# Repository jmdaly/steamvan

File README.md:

# SteamVan PCB

The SteamVan was developed as a MiniVan-compatible PCB based on an STM32MCU. It
does not support hot swap sockets, and it is designed such that the switches
are oriented such that the LEDs are South-facing.

## Overview

The SteamVan aims to meet the following design goals:

* Switches oriented such that the LEDs are South-facing, for
  compatibility with Cherry profile keycaps.

* USB Type-C support in both A to C and C to C configurations.

* QMK support.

* ESD protection circuitry, including data line protection and a
  polyfuse on the VCC line.

* Support for per-switch LED backlighting.

* Fits in MiniVan keyboard cases (tested with R3 MiniVan case only)

* RGB LED underglow support.

## Supported Layouts

The SteamVan supports the same layout options as the MiniVan.

## Obtaining the Files

This repository contains several submodules, which in turn contain
KiCad libraries used in the PCB design. In order to clone the SteamVan
repository, and all of the library submodules, the following command
must be issued,

```
git clone --recursive https://github.com/jmdaly/steamvan.git
```

## Acknowledgements

This project would not have been possible without all of the awesome work put
in by Evan Sailer of thevankeyboards.com. I own an R3 MiniVan and I love it. I
really like PCBs that have South-facing LEDs, USB-C connectors, and STM32
microcontrollers. As a result, I took on this project so that I could continue
to use the MiniVan layout, as well as my MiniVan case and keycaps, but have
some of the features that are important to me in a keyboard. I hope this work
is useful to other people.

There is an active keyboard design community on the MechKeys discord. The
users there have been very helpful, and I've learned a significant
amount about PCB design from them.

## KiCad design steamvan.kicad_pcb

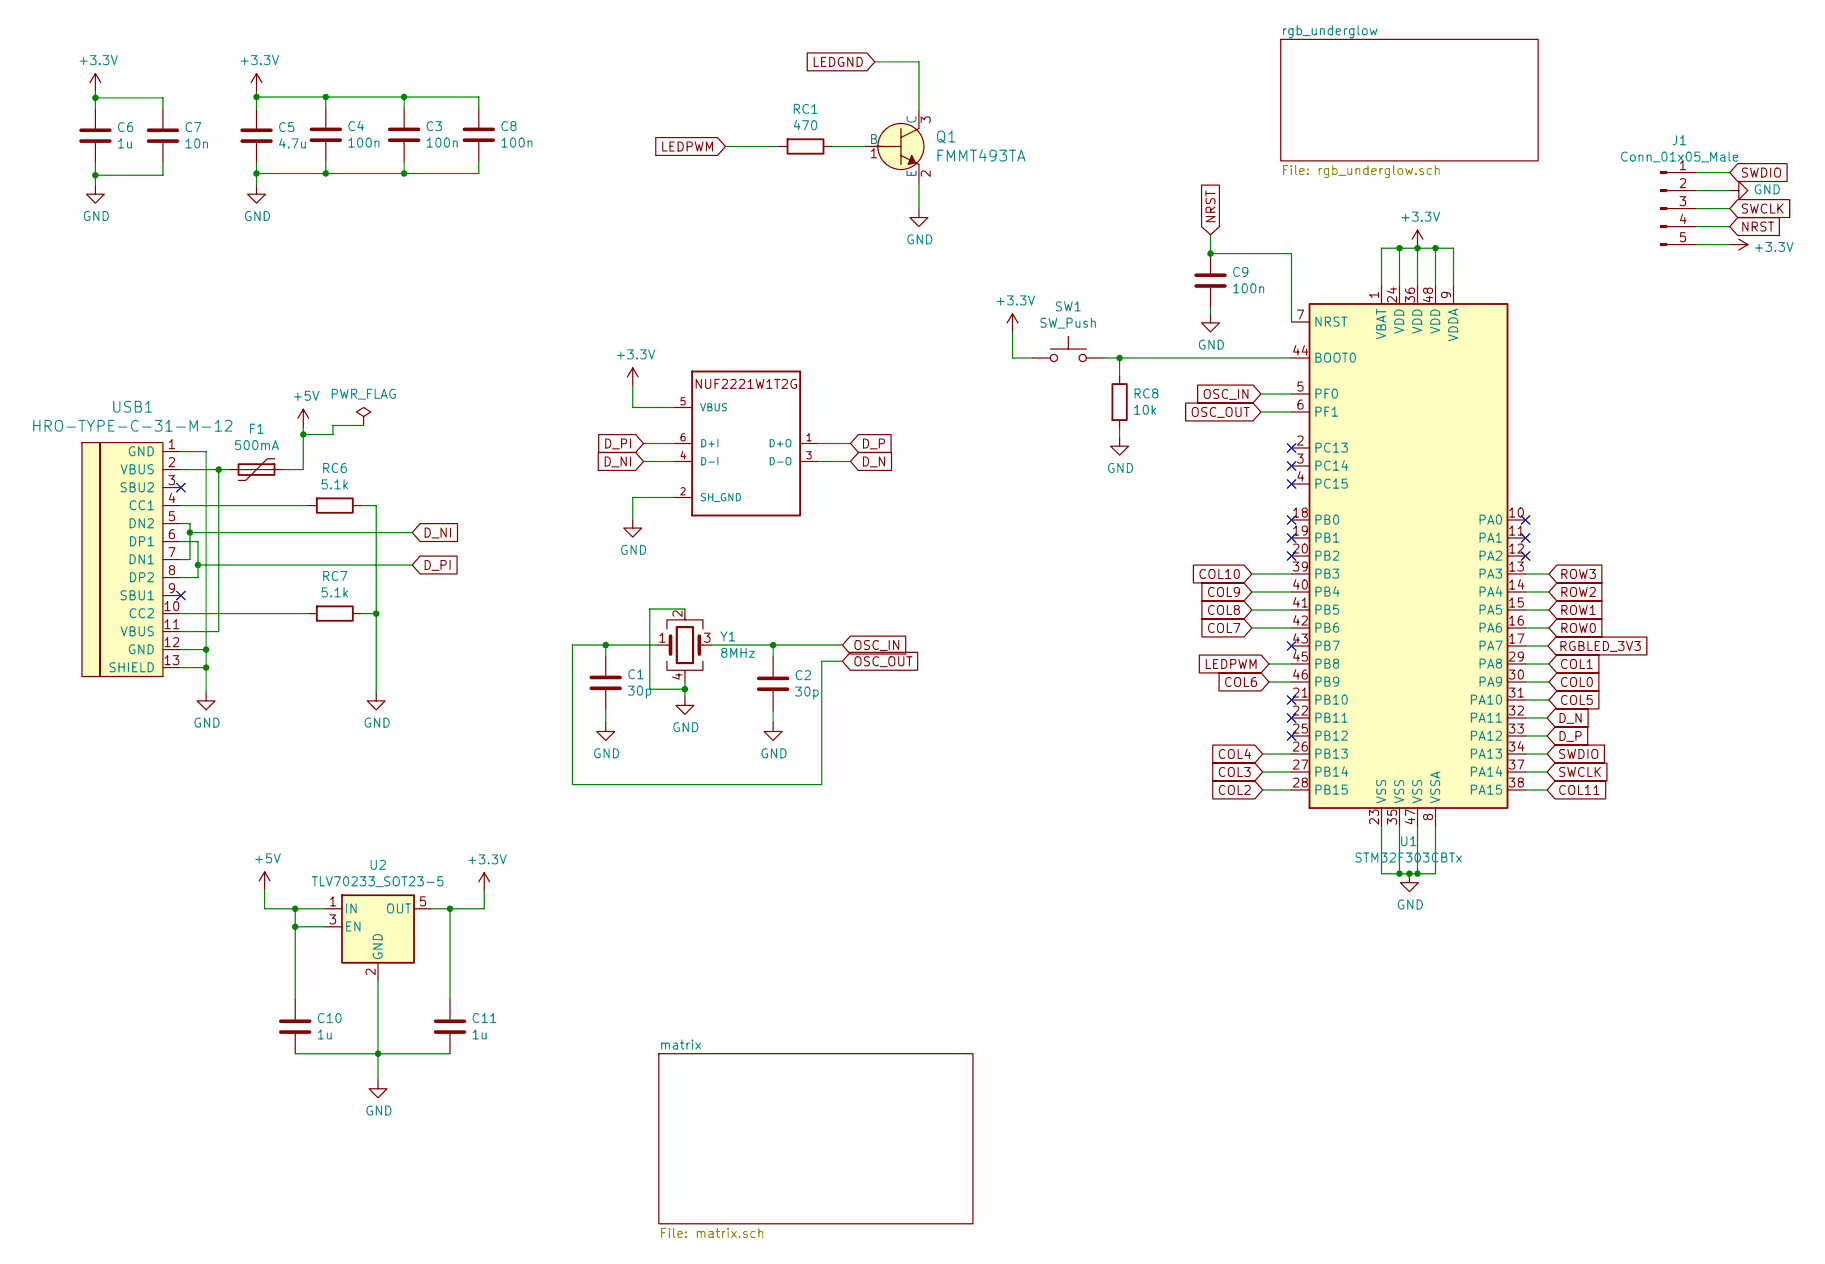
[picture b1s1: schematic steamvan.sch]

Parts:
C1, C2: 30p; C_0603_1608Metric; LCSC PN C22397
C3, C4, C8, C9: 100n; C_0603_1608Metric; LCSC PN C1590
C5: 4.7u; C_0603_1608Metric; LCSC PN C19666
C6, C10, C11: 1u; C_0603_1608Metric; LCSC PN C59782
C7: 10n; C_0603_1608Metric; LCSC PN C1589
F1: 500mA; R_0805_2012Metric; LCSC PN C66452
J1: Conn_01x05_Male; PinHeader_1x05_P2.54mm_Vertical
Q1: FMMT493TA; SOT-23-3; MPN FMMT493TA; Digi-Key_PN FMMT493CT-ND
RC1: 470; R_0603_1608Metric
RC6, RC7: 5.1k; R_0603_1608Metric; LCSC PN C14677
RC8: 10k; R_0603_1608Metric; LCSC PN C98220
SW1: SW_Push; SW_SPST_TL3342; LCSC PN C92584
U1: STM32F303CBTx; LQFP-48_7x7mm_P0.5mm; LCSC PN C108516
U2: TLV70233_SOT23-5; SOT-23-5; LCSC PN C26833
U3: NUF2221W1T2G; SOT-363; LCSC PN C274624
USB1: HRO-TYPE-C-31-M-12; HRO-TYPE-C-31-M-12-Assembly; LCSC PN C165948
Y1: 8MHz; Crystal_SMD_5032-4Pin_5.0x3.2mm; LCSC PN C133333

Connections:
+3V3: C3.1, C4.1, C5.1, C6.1, C7.1, C8.1, C11.1, J1.5, SW1.1, U1.1 (VBAT), U1.9 (VDDA), U1.24 (VDD), U1.36 (VDD), U1.48 (VDD), U2.5 (OUT), U3.5 (VBUS)
+5V: C10.1, F1.1, U2.1 (IN), U2.3 (EN); also elsewhere on the board
COL0: U1.30 (PA9); also elsewhere on the board
COL1: U1.29 (PA8); also elsewhere on the board
COL2: U1.28 (PB15); also elsewhere on the board
COL3: U1.27 (PB14); also elsewhere on the board
COL4: U1.26 (PB13); also elsewhere on the board
COL5: U1.31 (PA10); also elsewhere on the board
COL6: U1.46 (PB9); also elsewhere on the board
COL7: U1.42 (PB6); also elsewhere on the board
COL8: U1.41 (PB5); also elsewhere on the board
COL9: U1.40 (PB4); also elsewhere on the board
COL10: U1.39 (PB3); also elsewhere on the board
COL11: U1.38 (PA15); also elsewhere on the board
D_N: U1.32 (PA11), U3.3 (D-O)
D_NI: U3.4 (D-I), USB1.5 (DN2), USB1.7 (DN1)
D_P: U1.33 (PA12), U3.1 (D+O)
D_PI: U3.6 (D+I), USB1.6 (DP1), USB1.8 (DP2)
GND: C1.2, C2.2, C3.2, C4.2, C5.2, C6.2, C7.2, C8.2, C9.2, C10.2, C11.2, J1.2, Q1.2 (E), RC6.1, RC7.1, RC8.2, U1.8 (VSSA), U1.23 (VSS), U1.35 (VSS), U1.47 (VSS), U2.2 (GND), U3.2 (SH_GND), USB1.1 (GND), USB1.12 (GND), USB1.13 (SHIELD), Y1.2, Y1.4; also elsewhere on the board
LEDGND: Q1.3 (C); also elsewhere on the board
LEDPWM: RC1.2, U1.45 (PB8)
NRST: C9.1, J1.4, U1.7 (NRST)
unnamed: F1.2, USB1.2 (VBUS), USB1.11 (VBUS)
unnamed: Q1.1 (B), RC1.1
unnamed: RC6.2, USB1.4 (CC1)
unnamed: RC7.2, USB1.10 (CC2)
unnamed: RC8.1, SW1.2, U1.44 (BOOT0)
OSC_IN: C2.1, U1.5 (PF0), Y1.3
OSC_OUT: C1.1, U1.6 (PF1), Y1.1
RGBLED_3V3: U1.17 (PA7); also elsewhere on the board
ROW0: U1.16 (PA6); also elsewhere on the board
ROW1: U1.15 (PA5); also elsewhere on the board
ROW2: U1.14 (PA4); also elsewhere on the board
ROW3: U1.13 (PA3); also elsewhere on the board
SWCLK: J1.3, U1.37 (PA14)
SWDIO: J1.1, U1.34 (PA13)

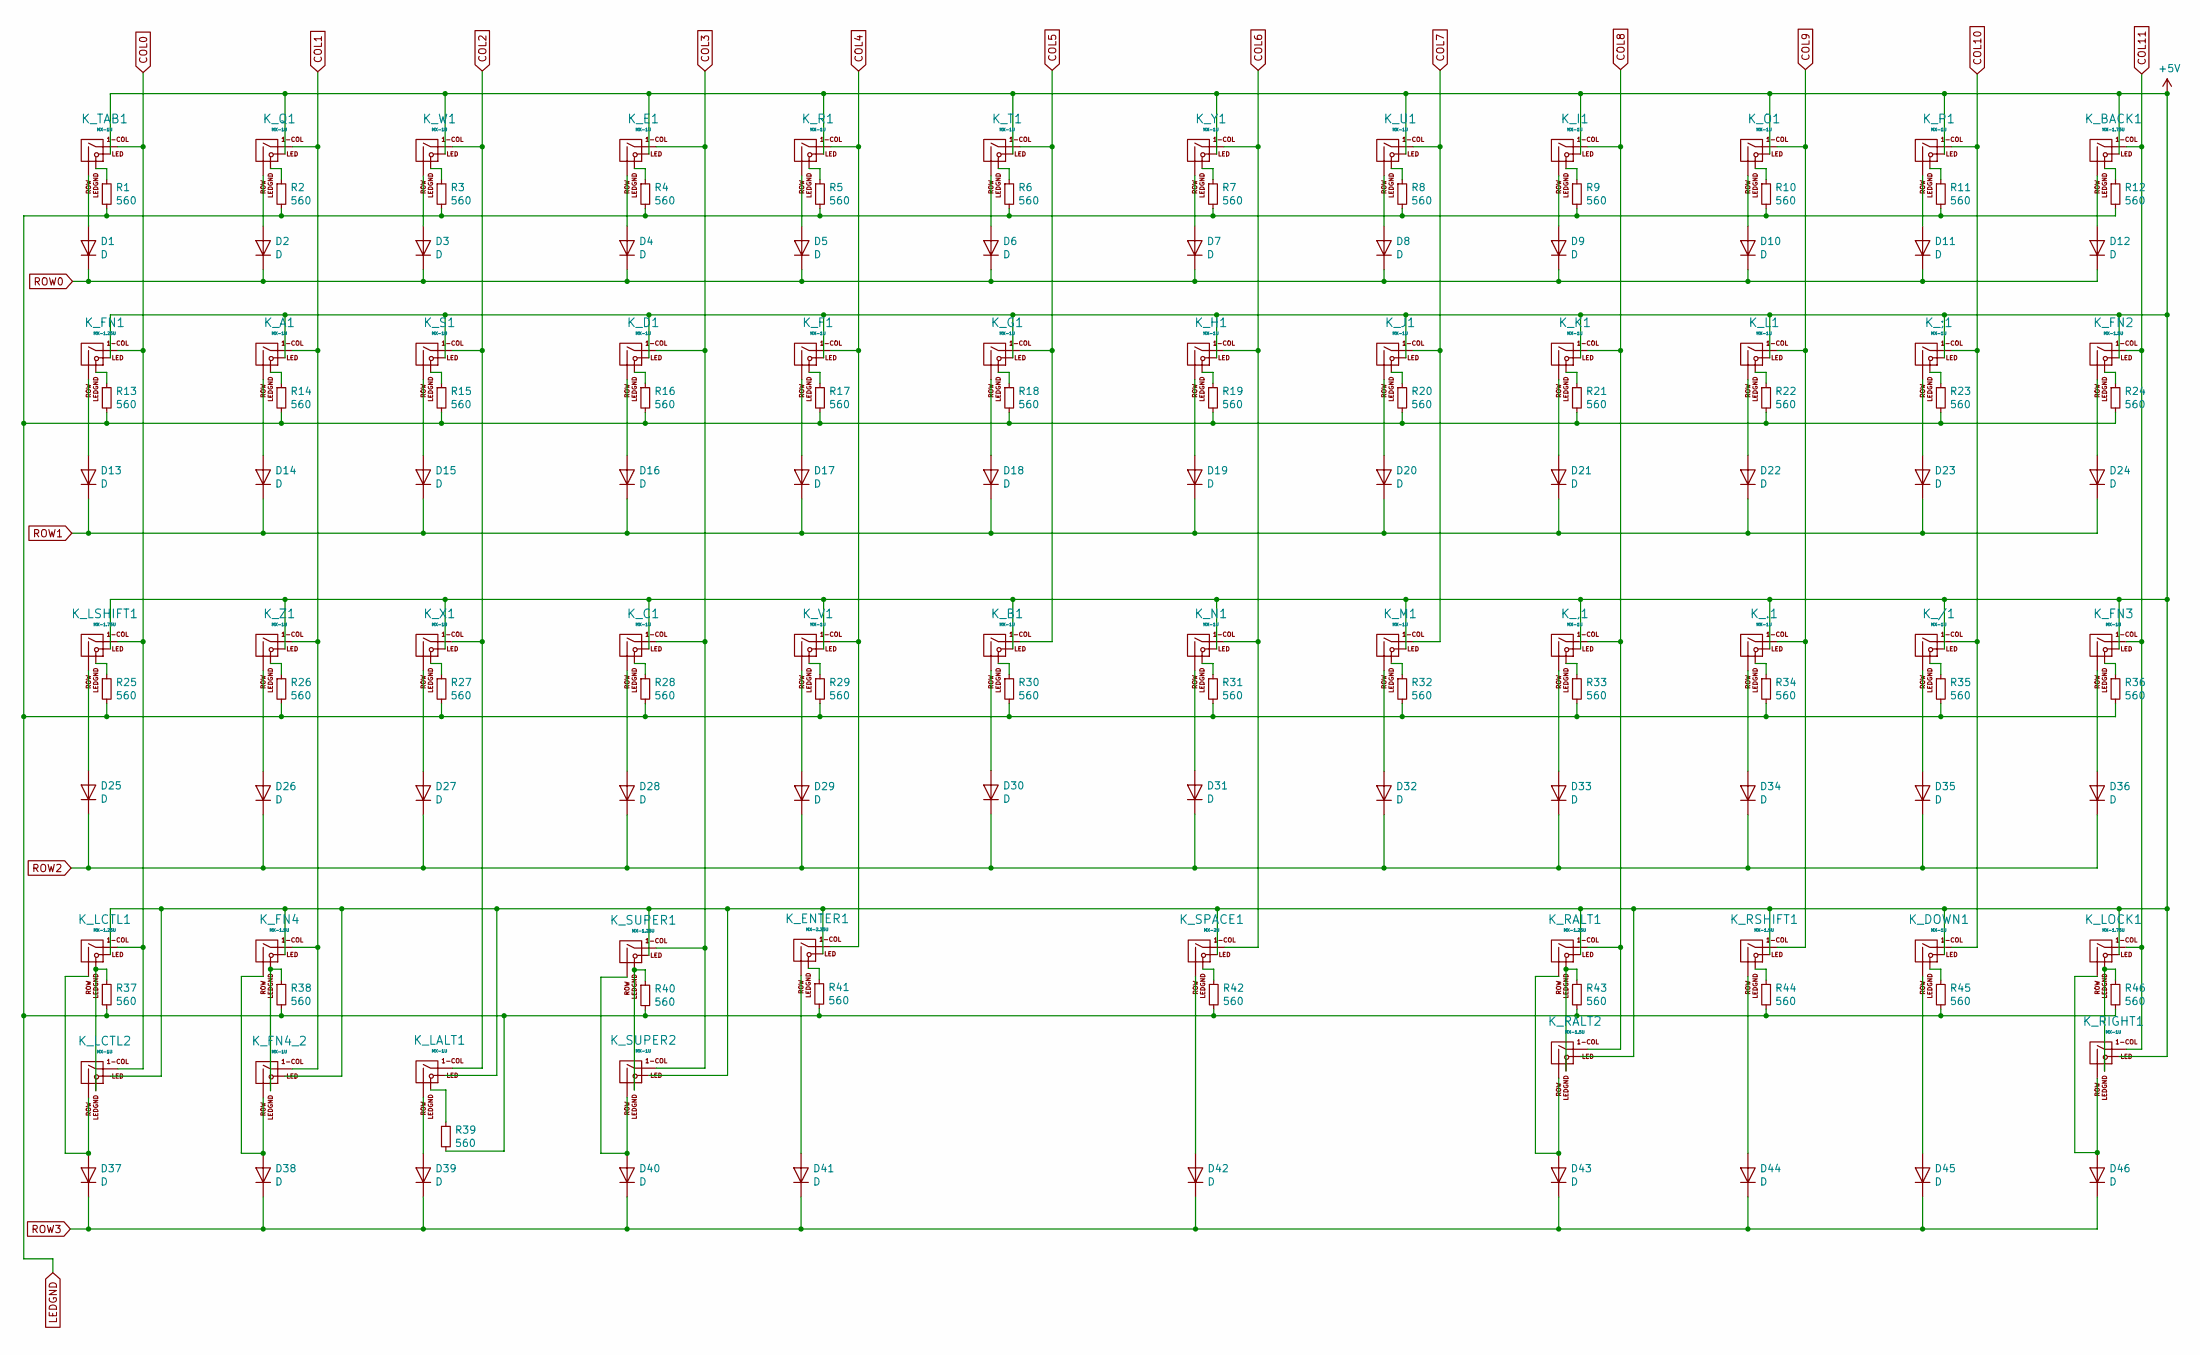
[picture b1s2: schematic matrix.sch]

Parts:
D1, D2, D3, D4, D5, D6, D7, D8, D9, D10, D11, D12, D13, D14, D15, D16, D17, D18, D19, D20, D21, D22, D23, D24, D25, D26, D27, D28, D29, D30, D31, D32, D33, D34, D35, D36, D37, D38, D39, D40, D41, D42, D43, D44, D45, D46: D; D_SOD-123; LCSC PN C83528
K_,1: MX-1U; MXOnly-1U
K_.1: MX-1U; MXOnly-1U
K_/1: MX-1U; MXOnly-1U
K_;1: MX-1U; MXOnly-1U
K_A1: MX-1U; MXOnly-1U
K_B1: MX-1U; MXOnly-1U
K_BACK1: MX-1.75U; MXOnly-1.75U
K_C1: MX-1U; MXOnly-1U
K_D1: MX-1U; MXOnly-1U
K_DOWN1: MX-1U; MXOnly-1U
K_E1: MX-1U; MXOnly-1U
K_ENTER1: MX-2.25U; MXOnly-2.25U-ReversedStabilizers
K_F1: MX-1U; MXOnly-1U
K_FN1: MX-1.25U; MXOnly-1.25U
K_FN2, K_FN4: MX-1.5U; MXOnly-1.5U
K_FN3, K_FN4_2: MX-1U; MXOnly-1U
K_G1: MX-1U; MXOnly-1U
K_H1: MX-1U; MXOnly-1U
K_I1: MX-1U; MXOnly-1U
K_J1: MX-1U; MXOnly-1U
K_K1: MX-1U; MXOnly-1U
K_L1: MX-1U; MXOnly-1U
K_LALT1: MX-1U; MXOnly-1U
K_LCTL1: MX-1.25U; MXOnly-1.25U
K_LCTL2: MX-1U; MXOnly-1U-FLIPPED
K_LOCK1: MX-1.75U; MXOnly-1.75U
K_LSHIFT1: MX-1.75U; MXOnly-1.75U
K_M1: MX-1U; MXOnly-1U
K_N1: MX-1U; MXOnly-1U
K_O1: MX-1U; MXOnly-1U
K_P1: MX-1U; MXOnly-1U
K_Q1: MX-1U; MXOnly-1U
K_R1: MX-1U; MXOnly-1U
K_RALT1: MX-1.25U; MXOnly-1.25U
K_RALT2: MX-1.5U; MXOnly-1.5U-FLIPPED
K_RIGHT1: MX-1U; MXOnly-1U
K_RSHIFT1: MX-1.5U; MXOnly-1.5U
K_S1: MX-1U; MXOnly-1U
K_SPACE1: MX-2U; MXOnly-2U-ReversedStabilizers
K_SUPER1: MX-1.25U; MXOnly-1.25U
K_SUPER2: MX-1U; MXOnly-1U-FLIPPED
K_T1: MX-1U; MXOnly-1U
K_TAB1: MX-1U; MXOnly-1U
K_U1: MX-1U; MXOnly-1U
K_V1: MX-1U; MXOnly-1U
K_W1: MX-1U; MXOnly-1U
K_X1: MX-1U; MXOnly-1U
K_Y1: MX-1U; MXOnly-1U
K_Z1: MX-1U; MXOnly-1U
R1, R2, R3, R4, R5, R6, R7, R8, R9, R10, R11, R12, R13, R14, R15, R16, R17, R18, R19, R20, R21, R22, R23, R24, R25, R26, R27, R28, R29, R30, R31, R32, R33, R34, R35, R36, R37, R38, R39, R40, R41, R42, R43, R44, R45, R46: 560; R_0603_1608Metric

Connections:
+5V: K_,1.3 (LED), K_.1.3 (LED), K_/1.3 (LED), K_;1.3 (LED), K_A1.3 (LED), K_B1.3 (LED), K_BACK1.3 (LED), K_C1.3 (LED), K_D1.3 (LED), K_DOWN1.3 (LED), K_E1.3 (LED), K_ENTER1.3 (LED), K_F1.3 (LED), K_FN1.3 (LED), K_FN2.3 (LED), K_FN3.3 (LED), K_FN4.3 (LED), K_FN4_2.3 (LED), K_G1.3 (LED), K_H1.3 (LED), K_I1.3 (LED), K_J1.3 (LED), K_K1.3 (LED), K_L1.3 (LED), K_LALT1.3 (LED), K_LCTL1.3 (LED), K_LCTL2.3 (LED), K_LOCK1.3 (LED), K_LSHIFT1.3 (LED), K_M1.3 (LED), K_N1.3 (LED), K_O1.3 (LED), K_P1.3 (LED), K_Q1.3 (LED), K_R1.3 (LED), K_RALT1.3 (LED), K_RALT2.3 (LED), K_RIGHT1.3 (LED), K_RSHIFT1.3 (LED), K_S1.3 (LED), K_SPACE1.3 (LED), K_SUPER1.3 (LED), K_SUPER2.3 (LED), K_T1.3 (LED), K_TAB1.3 (LED), K_U1.3 (LED), K_V1.3 (LED), K_W1.3 (LED), K_X1.3 (LED), K_Y1.3 (LED), K_Z1.3 (LED); also elsewhere on the board
COL0: K_FN1.1 (COL), K_LCTL1.1 (COL), K_LCTL2.1 (COL), K_LSHIFT1.1 (COL), K_TAB1.1 (COL); also elsewhere on the board
COL1: K_A1.1 (COL), K_FN4.1 (COL), K_FN4_2.1 (COL), K_Q1.1 (COL), K_Z1.1 (COL); also elsewhere on the board
COL2: K_LALT1.1 (COL), K_S1.1 (COL), K_W1.1 (COL), K_X1.1 (COL); also elsewhere on the board
COL3: K_C1.1 (COL), K_D1.1 (COL), K_E1.1 (COL), K_SUPER1.1 (COL), K_SUPER2.1 (COL); also elsewhere on the board
COL4: K_ENTER1.1 (COL), K_F1.1 (COL), K_R1.1 (COL), K_V1.1 (COL); also elsewhere on the board
COL5: K_B1.1 (COL), K_G1.1 (COL), K_T1.1 (COL); also elsewhere on the board
COL6: K_H1.1 (COL), K_N1.1 (COL), K_SPACE1.1 (COL), K_Y1.1 (COL); also elsewhere on the board
COL7: K_J1.1 (COL), K_M1.1 (COL), K_U1.1 (COL); also elsewhere on the board
COL8: K_,1.1 (COL), K_I1.1 (COL), K_K1.1 (COL), K_RALT1.1 (COL), K_RALT2.1 (COL); also elsewhere on the board
COL9: K_.1.1 (COL), K_L1.1 (COL), K_O1.1 (COL), K_RSHIFT1.1 (COL); also elsewhere on the board
COL10: K_/1.1 (COL), K_;1.1 (COL), K_DOWN1.1 (COL), K_P1.1 (COL); also elsewhere on the board
COL11: K_BACK1.1 (COL), K_FN2.1 (COL), K_FN3.1 (COL), K_LOCK1.1 (COL), K_RIGHT1.1 (COL); also elsewhere on the board
LEDGND: R1.2, R2.2, R3.2, R4.2, R5.2, R6.2, R7.2, R8.2, R9.2, R10.2, R11.2, R12.2, R13.2, R14.2, R15.2, R16.2, R17.2, R18.2, R19.2, R20.2, R21.2, R22.2, R23.2, R24.2, R25.2, R26.2, R27.2, R28.2, R29.2, R30.2, R31.2, R32.2, R33.2, R34.2, R35.2, R36.2, R37.2, R38.2, R39.2, R40.2, R41.2, R42.2, R43.2, R44.2, R45.2, R46.2; also elsewhere on the board
unnamed: D1.2 (A), K_TAB1.2 (ROW)
unnamed: D2.2 (A), K_Q1.2 (ROW)
unnamed: D3.2 (A), K_W1.2 (ROW)
unnamed: D4.2 (A), K_E1.2 (ROW)
unnamed: D5.2 (A), K_R1.2 (ROW)
unnamed: D6.2 (A), K_T1.2 (ROW)
unnamed: D7.2 (A), K_Y1.2 (ROW)
unnamed: D8.2 (A), K_U1.2 (ROW)
unnamed: D9.2 (A), K_I1.2 (ROW)
unnamed: D10.2 (A), K_O1.2 (ROW)
unnamed: D11.2 (A), K_P1.2 (ROW)
unnamed: D12.2 (A), K_BACK1.2 (ROW)
unnamed: D13.2 (A), K_FN1.2 (ROW)
unnamed: D14.2 (A), K_A1.2 (ROW)
unnamed: D15.2 (A), K_S1.2 (ROW)
unnamed: D16.2 (A), K_D1.2 (ROW)
unnamed: D17.2 (A), K_F1.2 (ROW)
unnamed: D18.2 (A), K_G1.2 (ROW)
unnamed: D19.2 (A), K_H1.2 (ROW)
unnamed: D20.2 (A), K_J1.2 (ROW)
unnamed: D21.2 (A), K_K1.2 (ROW)
unnamed: D22.2 (A), K_L1.2 (ROW)
unnamed: D23.2 (A), K_;1.2 (ROW)
unnamed: D24.2 (A), K_FN2.2 (ROW)
unnamed: D25.2 (A), K_LSHIFT1.2 (ROW)
unnamed: D26.2 (A), K_Z1.2 (ROW)
unnamed: D27.2 (A), K_X1.2 (ROW)
unnamed: D28.2 (A), K_C1.2 (ROW)
unnamed: D29.2 (A), K_V1.2 (ROW)
unnamed: D30.2 (A), K_B1.2 (ROW)
unnamed: D31.2 (A), K_N1.2 (ROW)
unnamed: D32.2 (A), K_M1.2 (ROW)
unnamed: D33.2 (A), K_,1.2 (ROW)
unnamed: D34.2 (A), K_.1.2 (ROW)
unnamed: D35.2 (A), K_/1.2 (ROW)
unnamed: D36.2 (A), K_FN3.2 (ROW)
unnamed: D37.2 (A), K_LCTL1.2 (ROW), K_LCTL2.2 (ROW)
unnamed: D38.2 (A), K_FN4.2 (ROW), K_FN4_2.2 (ROW)
unnamed: D39.2 (A), K_LALT1.2 (ROW)
unnamed: D40.2 (A), K_SUPER1.2 (ROW), K_SUPER2.2 (ROW)
unnamed: D41.2 (A), K_ENTER1.2 (ROW)
unnamed: D42.2 (A), K_SPACE1.2 (ROW)
unnamed: D43.2 (A), K_RALT1.2 (ROW), K_RALT2.2 (ROW)
unnamed: D44.2 (A), K_RSHIFT1.2 (ROW)
unnamed: D45.2 (A), K_DOWN1.2 (ROW)
unnamed: D46.2 (A), K_LOCK1.2 (ROW), K_RIGHT1.2 (ROW)
unnamed: K_,1.4 (LEDGND), R33.1
unnamed: K_.1.4 (LEDGND), R34.1
unnamed: K_/1.4 (LEDGND), R35.1
unnamed: K_;1.4 (LEDGND), R23.1
unnamed: K_A1.4 (LEDGND), R14.1
unnamed: K_B1.4 (LEDGND), R30.1
unnamed: K_BACK1.4 (LEDGND), R12.1
unnamed: K_C1.4 (LEDGND), R28.1
unnamed: K_D1.4 (LEDGND), R16.1
unnamed: K_DOWN1.4 (LEDGND), R45.1
unnamed: K_E1.4 (LEDGND), R4.1
unnamed: K_ENTER1.4 (LEDGND), R41.1
unnamed: K_F1.4 (LEDGND), R17.1
unnamed: K_FN1.4 (LEDGND), R13.1
unnamed: K_FN2.4 (LEDGND), R24.1
unnamed: K_FN3.4 (LEDGND), R36.1
unnamed: K_FN4.4 (LEDGND), K_FN4_2.4 (LEDGND), R38.1
unnamed: K_G1.4 (LEDGND), R18.1
unnamed: K_H1.4 (LEDGND), R19.1
unnamed: K_I1.4 (LEDGND), R9.1
unnamed: K_J1.4 (LEDGND), R20.1
unnamed: K_K1.4 (LEDGND), R21.1
unnamed: K_L1.4 (LEDGND), R22.1
unnamed: K_LALT1.4 (LEDGND), R39.1
unnamed: K_LCTL1.4 (LEDGND), K_LCTL2.4 (LEDGND), R37.1
unnamed: K_LOCK1.4 (LEDGND), K_RIGHT1.4 (LEDGND), R46.1
unnamed: K_LSHIFT1.4 (LEDGND), R25.1
unnamed: K_M1.4 (LEDGND), R32.1
unnamed: K_N1.4 (LEDGND), R31.1
unnamed: K_O1.4 (LEDGND), R10.1
unnamed: K_P1.4 (LEDGND), R11.1
unnamed: K_Q1.4 (LEDGND), R2.1
unnamed: K_R1.4 (LEDGND), R5.1
unnamed: K_RALT1.4 (LEDGND), K_RALT2.4 (LEDGND), R43.1
unnamed: K_RSHIFT1.4 (LEDGND), R44.1
unnamed: K_S1.4 (LEDGND), R15.1
unnamed: K_SPACE1.4 (LEDGND), R42.1
unnamed: K_SUPER1.4 (LEDGND), K_SUPER2.4 (LEDGND), R40.1
unnamed: K_T1.4 (LEDGND), R6.1
unnamed: K_TAB1.4 (LEDGND), R1.1
unnamed: K_U1.4 (LEDGND), R8.1
unnamed: K_V1.4 (LEDGND), R29.1
unnamed: K_W1.4 (LEDGND), R3.1
unnamed: K_X1.4 (LEDGND), R27.1
unnamed: K_Y1.4 (LEDGND), R7.1
unnamed: K_Z1.4 (LEDGND), R26.1
ROW0: D1.1 (K), D2.1 (K), D3.1 (K), D4.1 (K), D5.1 (K), D6.1 (K), D7.1 (K), D8.1 (K), D9.1 (K), D10.1 (K), D11.1 (K), D12.1 (K); also elsewhere on the board
ROW1: D13.1 (K), D14.1 (K), D15.1 (K), D16.1 (K), D17.1 (K), D18.1 (K), D19.1 (K), D20.1 (K), D21.1 (K), D22.1 (K), D23.1 (K), D24.1 (K); also elsewhere on the board
ROW2: D25.1 (K), D26.1 (K), D27.1 (K), D28.1 (K), D29.1 (K), D30.1 (K), D31.1 (K), D32.1 (K), D33.1 (K), D34.1 (K), D35.1 (K), D36.1 (K); also elsewhere on the board
ROW3: D37.1 (K), D38.1 (K), D39.1 (K), D40.1 (K), D41.1 (K), D42.1 (K), D43.1 (K), D44.1 (K), D45.1 (K), D46.1 (K); also elsewhere on the board

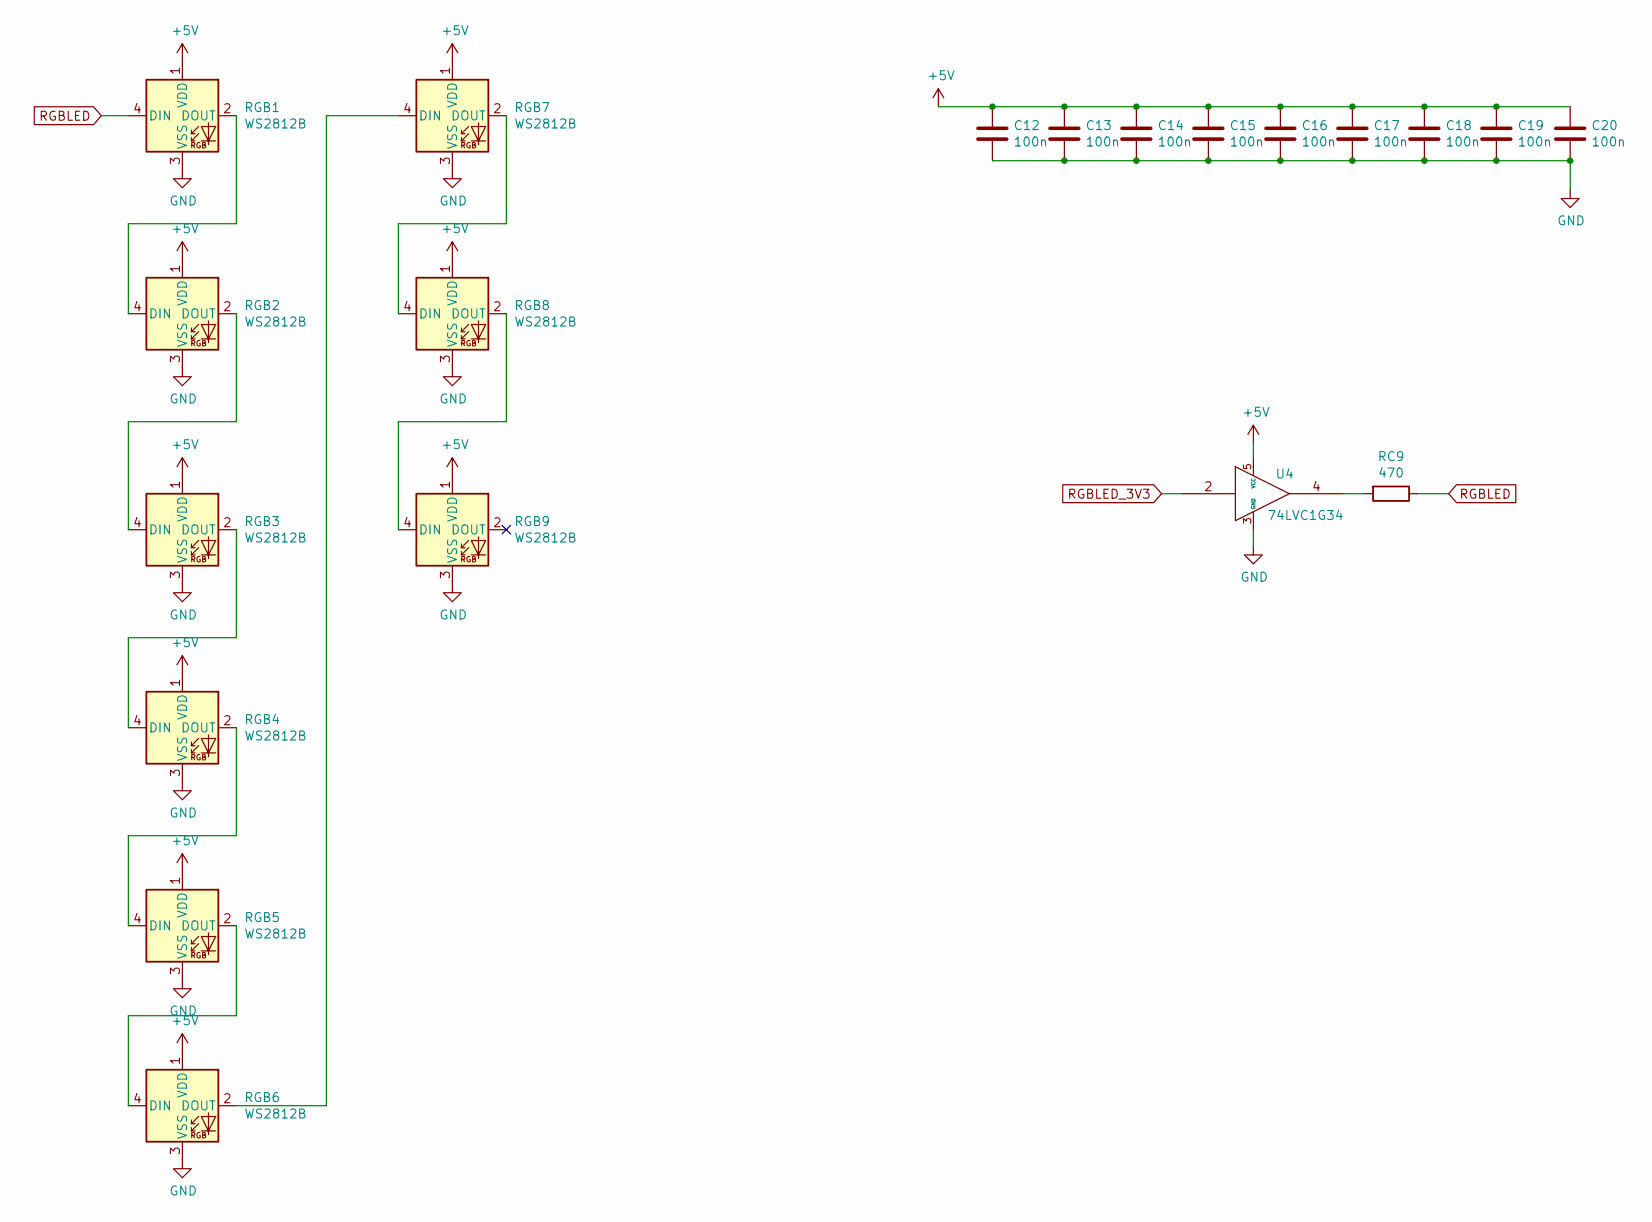
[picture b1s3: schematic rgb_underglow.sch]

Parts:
C12, C13, C14, C15, C16, C17, C18, C19, C20: 100n; C_0603_1608Metric; LCSC PN C1590
RC9: 470; R_0603_1608Metric; LCSC PN C114433
RGB1, RGB2, RGB3, RGB4, RGB5, RGB6, RGB7, RGB8, RGB9: WS2812B; LED_WS2812B_PLCC4_5.0x5.0mm_P3.2mm; LCSC PN C114585
U4: 74LVC1G34; SOT-353_SC-70-5; LCSC PN C94111

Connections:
+5V: C12.1, C13.1, C14.1, C15.1, C16.1, C17.1, C18.1, C19.1, C20.1, RGB1.1 (VDD), RGB2.1 (VDD), RGB3.1 (VDD), RGB4.1 (VDD), RGB5.1 (VDD), RGB6.1 (VDD), RGB7.1 (VDD), RGB8.1 (VDD), RGB9.1 (VDD), U4.5 (VCC); also elsewhere on the board
GND: C12.2, C13.2, C14.2, C15.2, C16.2, C17.2, C18.2, C19.2, C20.2, RGB1.3 (VSS), RGB2.3 (VSS), RGB3.3 (VSS), RGB4.3 (VSS), RGB5.3 (VSS), RGB6.3 (VSS), RGB7.3 (VSS), RGB8.3 (VSS), RGB9.3 (VSS), U4.3 (GND); also elsewhere on the board
unnamed: RC9.2, U4.4
unnamed: RGB1.2 (DOUT), RGB2.4 (DIN)
unnamed: RGB2.2 (DOUT), RGB3.4 (DIN)
unnamed: RGB3.2 (DOUT), RGB4.4 (DIN)
unnamed: RGB4.2 (DOUT), RGB5.4 (DIN)
unnamed: RGB5.2 (DOUT), RGB6.4 (DIN)
unnamed: RGB6.2 (DOUT), RGB7.4 (DIN)
unnamed: RGB7.2 (DOUT), RGB8.4 (DIN)
unnamed: RGB8.2 (DOUT), RGB9.4 (DIN)
RGBLED: RC9.1, RGB1.4 (DIN)
RGBLED_3V3: U4.2; also elsewhere on the board

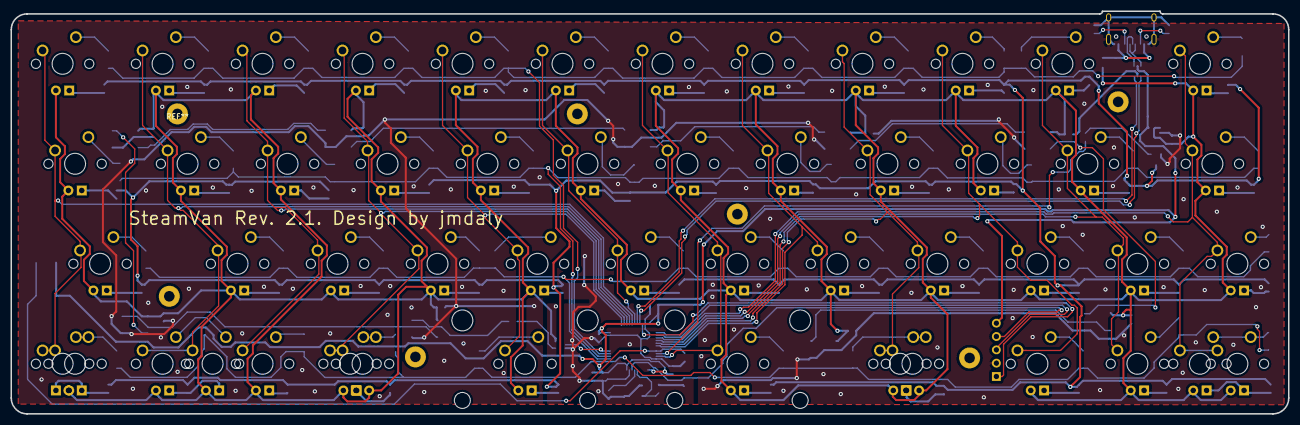
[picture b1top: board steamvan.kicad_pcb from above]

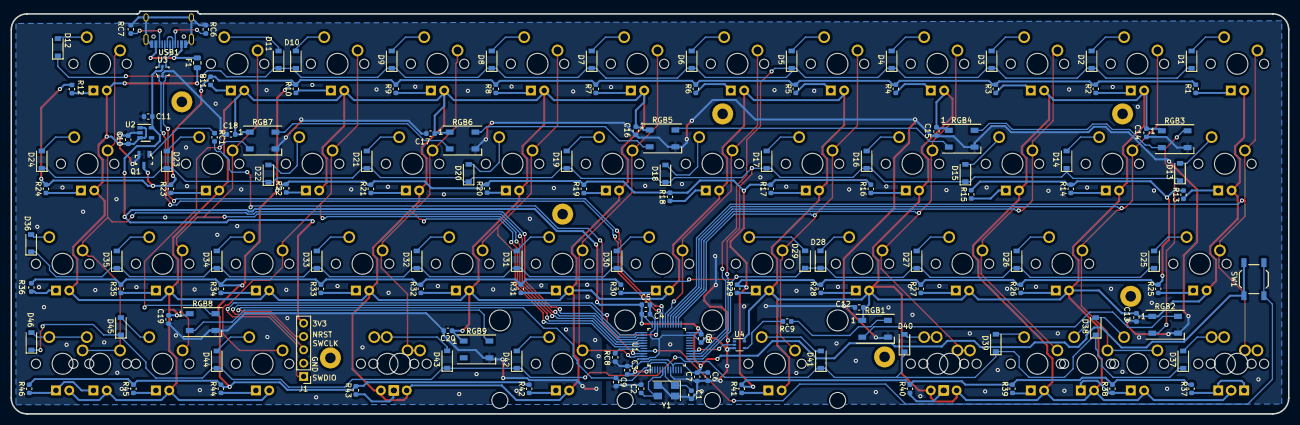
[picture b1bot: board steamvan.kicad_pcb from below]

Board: 2 copper layers, 243.4 x 76.7 mm, 187 parts (136 on the bottom side), 138 nets.

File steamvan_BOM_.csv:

References,Part,Value,Footprint,Quantity Per PCB,Digi-Key_PN,Datasheet,Description,LCSC PN,Product,Category,Status,Family,MPN,DK_Datasheet_Link,DK_Detail_Page,Manufacturer,Field8,Field4,Field7,Field6,Field5
C3 C4 C8 C9 C12 C13 C14 C15 C16 C17 C18 C19 C20,C,100n,C_0603_1608Metric,13,,~,Unpolarized capacitor,C1590,,,,,,,,,,,,,
C7,C,10n,C_0603_1608Metric,1,,~,Unpolarized capacitor,C1589,,,,,,,,,,,,,
C6 C10 C11,C,1u,C_0603_1608Metric,3,,~,Unpolarized capacitor,C59782,,,,,,,,,,,,,
C1 C2,C,30p,C_0603_1608Metric,2,,~,Unpolarized capacitor,C22397,,,,,,,,,,,,,
C5,C,4.7u,C_0603_1608Metric,1,,~,Unpolarized capacitor,C19666,,,,,,,,,,,,,
D1 D2 D3 D4 D5 D6 D7 D8 D9 D10 D11 D12 D13 D14 D15 D16 D17 D18 D19 D20 D21 D22 D23 D24 D25 D26 D27 D28 D29 D30 D31 D32 D33 D34 D35 D36 D37 D38 D39 D40 D41 D42 D43 D44 D45 D46,D,D,D_SOD-123,46,,http://www.mccsemi.com/up_pdf/1N4148W(SOD123).pdf,Diode,C83528,1N4148W-TP,,,,,,,,,,,,
F1,Polyfuse,500mA,R_0805_2012Metric,1,,~,"Resettable fuse, polymeric positive temperature coefficient",C66452,,,,,,,,,,,,,
J1,Conn_01x05_Male,Conn_01x05_Male,PinHeader_1x05_P2.54mm_Vertical,1,,~,"Generic connector, single row, 01x05, script generated (kicad-library-utils/schlib/autogen/connector/)",,,,,,,,,,,,,,
K_FN1 K_LCTL1 K_RALT1 K_SUPER1,MX-1.25U,MX-1.25U,MXOnly-1.25U,4,,,,,,,,,,,,,,,,,
K_FN2 K_FN4 K_RSHIFT1,MX-1.5U,MX-1.5U,MXOnly-1.5U,3,,,,,,,,,,,,,,,,,
K_RALT2,MX-1.5U,MX-1.5U,MXOnly-1.5U-FLIPPED,1,,,,,,,,,,,,,,,,,
K_BACK1 K_LSHIFT1,MX-1.75U,MX-1.75U,MXOnly-1.75U,2,,,,,,,,,,,,,,,,,
K_LOCK1,MX-1U,MX-1.75U,MXOnly-1.75U,1,,,,,,,,,,,,,,,,,
"K_,1 K_.1 K_/1 K_;1 K_A1 K_B1 K_C1 K_D1 K_DOWN1 K_E1 K_F1 K_FN3 K_FN4_2 K_G1 K_H1 K_I1 K_J1 K_K1 K_L1 K_LALT1 K_M1 K_N1 K_O1 K_P1 K_Q1 K_R1 K_S1 K_T1 K_TAB1 K_U1 K_V1 K_W1 K_X1 K_Y1 K_Z1",MX-1U,MX-1U,MXOnly-1U,35,,,,,,,,,,,,,,,,,
K_LCTL2 K_SUPER2,MX-1U,MX-1U,MXOnly-1U-FLIPPED,2,,,,,,,,,,,,,,,,,
K_RIGHT1,MX-1.75U,MX-1U,MXOnly-1U,1,,,,,,,,,,,,,,,,,
K_ENTER1,MX-2.25U,MX-2.25U,MXOnly-2.25U-ReversedStabilizers,1,,,,,,,,,,,,,,,,,
K_SPACE1,MX-2U,MX-2U,MXOnly-2U-ReversedStabilizers,1,,,,,,,,,,,,,,,,,
Q1,FMMT493TA,FMMT493TA,SOT-23-3,1,FMMT493CT-ND,https://www.diodes.com/assets/Datasheets/FMMT493.pdf,TRANS NPN 100V 1A SOT23-3,C47296,,Discrete Semiconductor Products,Active,Transistors - Bipolar (BJT) - Single,FMMT493TA,https://www.diodes.com/assets/Datasheets/FMMT493.pdf,/product-detail/en/diodes-incorporated/FMMT493TA/FMMT493CT-ND/92663,Diodes Incorporated,,,,,
R1 R2 R3 R4 R5 R6 R7 R8 R9 R10 R11 R12 R13 R14 R15 R16 R17 R18 R19 R20 R21 R22 R23 R24 R25 R26 R27 R28 R29 R30 R31 R32 R33 R34 R35 R36 R37 R38 R39 R40 R41 R42 R43 R44 R45 R46,R_Small,560,R_0603_1608Metric,46,,~,"Resistor, small symbol",,,,,,,,,,,,,,
RC8,R,10k,R_0603_1608Metric,1,,~,Resistor,C98220,,,,,,,,,,,,,
RC1 RC9,R,470,R_0603_1608Metric,2,,~,Resistor,C114433,,,,,,,,,,,,,
RC6 RC7,R,5.1k,R_0603_1608Metric,2,,~,Resistor,C14677,,,,,,,,,,,,,
RGB1 RGB2 RGB3 RGB4 RGB5 RGB6 RGB7 RGB8 RGB9,WS2812B,WS2812B,LED_WS2812B_PLCC4_5.0x5.0mm_P3.2mm,9,,https://cdn-shop.adafruit.com/datasheets/WS2812B.pdf,RGB LED with integrated controller,C114585,,,,,,,,,,,,,
SW1,SW_Push,SW_Push,SW_SPST_TL3342,1,,,"Push button switch, generic, two pins",C92584,,,,,,,,,,,,,
U4,74LVC1G34,74LVC1G34,SOT-353_SC-70-5,1,,,,C94111,,,,,,,,,,,,,
U3,NUF2221W1T2G,NUF2221W1T2G,SOT-363,1,,Good,,C274624,,,,,,,,,ON Semiconductor,SOT-363 ON Semiconductor,NUF2221W1T2G Series 8 V USB Upstream Terminator with ESD Protection - SC-88,0.27 USD,NUF2221W1T2G
U1,STM32F303CBTx,STM32F303CBTx,LQFP-48_7x7mm_P0.5mm,1,,http://www.st.com/st-web-ui/static/active/en/resource/techni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,"ARM Cortex-M4 MCU, 128KB flash, 32KB RAM, 72MHz, 2-3.6V, 37 GPIO, LQFP-48",C108516,,,,,,,,,,,,,
U2,TLV70233_SOT23-5,TLV70233_SOT23-5,SOT-23-5,1,,http://www.ti.com/lit/ds/symlink/tlv702.pdf,"300 mA Low Dropout Voltage Regulator, Fixed Output 3.3V, SOT-23-5",C26833,,,,,,,,,,,,,
USB1,HRO-TYPE-C-31-M-12,HRO-TYPE-C-31-M-12,HRO-TYPE-C-31-M-12-Assembly,1,,,,C165948,,,,,,,,,,,,,
Y1,Crystal_GND24,8MHz,Crystal_SMD_5032-4Pin_5.0x3.2mm,1,,~,"Four pin crystal, GND on pins 2 and 4",C133333,,,,,,,,,,,,,





Component Groups:,31
Component Count:,187
Fitted Components:,187
Number of PCBs:,1
Total components:,187
Schematic Version:,
Schematic Date:,
BoM Date:,Sat 25 May 2019 10:14:55 PM EDT
Schematic Source:,/home/jmdaly/git/steamvan/steamvan.sch
KiCad Version:,Eeschema 5.0.2-bee76a0~70~ubuntu16.04.1

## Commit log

2018-12-23 Add: Initial addition of submodules
2018-12-23 Add: Initial commit of project structure
2018-12-23 Add: Digikey KiCAD library
2018-12-24 Update: Work on schematic
2018-12-27 Update: Work on board schematix. Not done yet
2018-12-27 Update: Finish preliminary work on schematic
    Schematic still needs review, and my pin choices for the
    matrix should be double checked.
2019-01-20 Add: new minivan layouts, and start switching to MX/Alps hybrid footprints
2019-01-20 Update: Work on PCB component placement
2019-01-26 Update: Work on PCB layout
2019-02-03 Add: PCB footprint
2019-02-04 Update: PCB footprint, and work on component placement
2019-02-05 Update: Work on routing
2019-02-13 Update: Add schematic components for RGB underglow, and work on routing
2019-02-18 Update: Work on underglow
2019-02-21 Update: More work on routing
2019-03-08 Update: More routing
2019-03-13 Update: Finish routing
2019-03-14 Update: Work on ground plane
2019-03-15 Update: Work on ground plane and exclusion around MCU
2019-03-18 Update: Routing improvements
2019-03-23 Update: More routing work
2019-03-23 Update: Work on routing and generate Gerbers
2019-05-10 Update: Gerbers
2019-05-15 Update: Move USB port location
2019-05-16 Update: silk screen
2019-05-17 Update: minor routing tweaks
2019-05-22 Update: Regenerate Gerbers prior to sending off to production
2019-05-22 Add: BOM
2019-05-26 Add: LCSC part numbers to schematic
2019-05-31 Update: Move components that may interfere with case
2019-06-01 Update: Keep components out of the way of the case
2019-06-10 Update: Begin moving RGB LEDs farther down
    I have done the three LEDs farthest from the USB port on the top row so
    far. Two more to go.
2019-06-11 Update: Move remaining RGB LEDs farther down to avoid case
2019-06-18 Update: Move reset switch to line up better with case
2019-06-20 Add: Initial standard plate
2019-06-20 Update: Move reset switch in from edge a bit
2019-06-27 Update: move programming headers - also regenerate Gerbers
2019-06-27 Update: adjust top row RGB LEDs
2019-07-09 Update: move programming jumper
2019-07-11 Update: Move more components
2019-08-03 Update: Gerbers and drill files
2019-08-07 Update: README
2019-12-09 Add: permissive license
2020-02-09 Update: Files for KiCad 5.1
2020-03-28 Update: Use public URL for keyboard parts lib
2020-05-06 Update: Rename gerbers for new convention
